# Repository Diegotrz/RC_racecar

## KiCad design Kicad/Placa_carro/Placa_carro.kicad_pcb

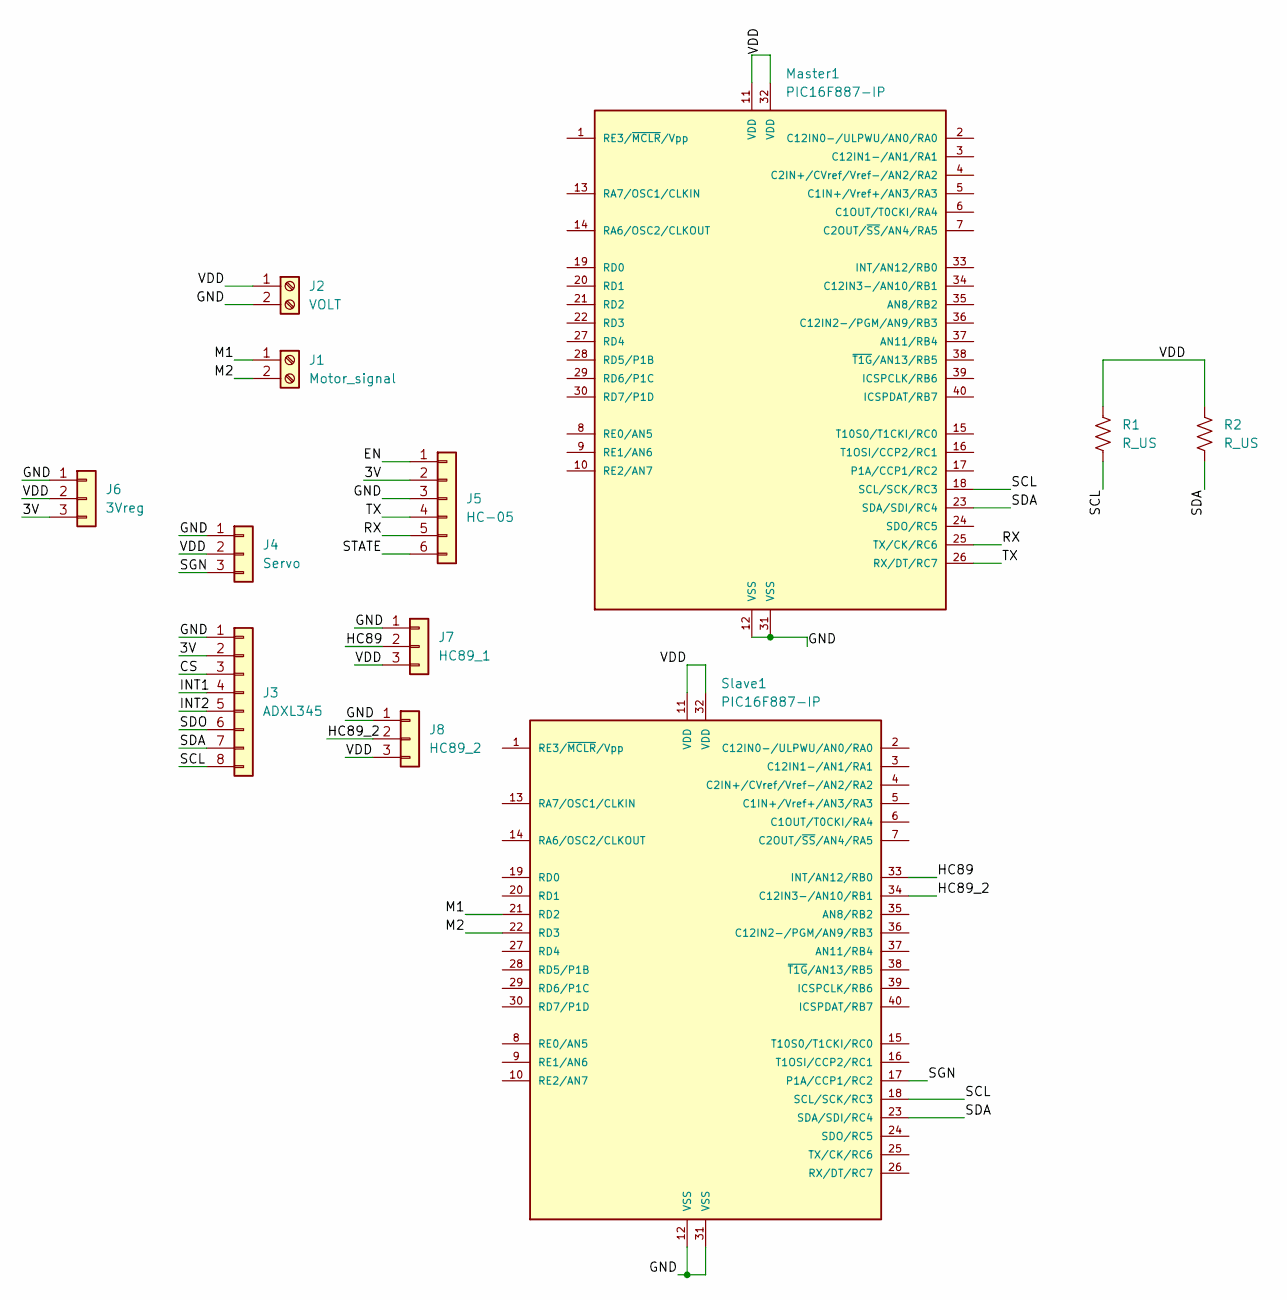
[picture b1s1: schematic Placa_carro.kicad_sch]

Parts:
J1: Motor_signal; TerminalBlock_bornier-2_P5.08mm
J2: VOLT; TerminalBlock_bornier-2_P5.08mm
J3: ADXL345; PinSocket_1x08_P2.54mm_Vertical
J4: Servo; PinHeader_1x03_P2.54mm_Vertical
J5: HC-05; PinSocket_1x06_P2.54mm_Vertical
J6: 3Vreg; PinHeader_1x03_P2.54mm_Vertical
J7: HC89_1; PinHeader_1x03_P2.54mm_Vertical
J8: HC89_2; PinHeader_1x03_P2.54mm_Vertical
Master1: PIC16F887-IP; DIP-40_W15.24mm
R1, R2: R_US; R_Axial_DIN0309_L9.0mm_D3.2mm_P12.70mm_Horizontal
Slave1: PIC16F887-IP; DIP-40_W15.24mm

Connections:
/3V: J3.2, J5.2, J6.3
/CS: J3.3
/EN: J5.1
/GND: J2.2, J3.1, J4.1, J5.3, J6.1, J7.1, J8.1, Master1.12 (VSS), Master1.31 (VSS), Slave1.12 (VSS), Slave1.31 (VSS)
/HC89: J7.2, Slave1.33 (INT/AN12/RB0)
/HC89_2: J8.2, Slave1.34 (C12IN3-/AN10/RB1)
/INT1: J3.4
/INT2: J3.5
/M1: J1.1, Slave1.21 (RD2)
/M2: J1.2, Slave1.22 (RD3)
/RX: J5.5, Master1.25 (TX/CK/RC6)
/SCL: J3.8, Master1.18 (SCL/SCK/RC3), R1.2, Slave1.18 (SCL/SCK/RC3)
/SDA: J3.7, Master1.23 (SDA/SDI/RC4), R2.2, Slave1.23 (SDA/SDI/RC4)
/SDO: J3.6
/SGN: J4.3, Slave1.17 (P1A/CCP1/RC2)
/STATE: J5.6
/TX: J5.4, Master1.26 (RX/DT/RC7)
/VDD: J2.1, J4.2, J6.2, J7.3, J8.3, Master1.11 (VDD), Master1.32 (VDD), R1.1, R2.1, Slave1.11 (VDD), Slave1.32 (VDD)

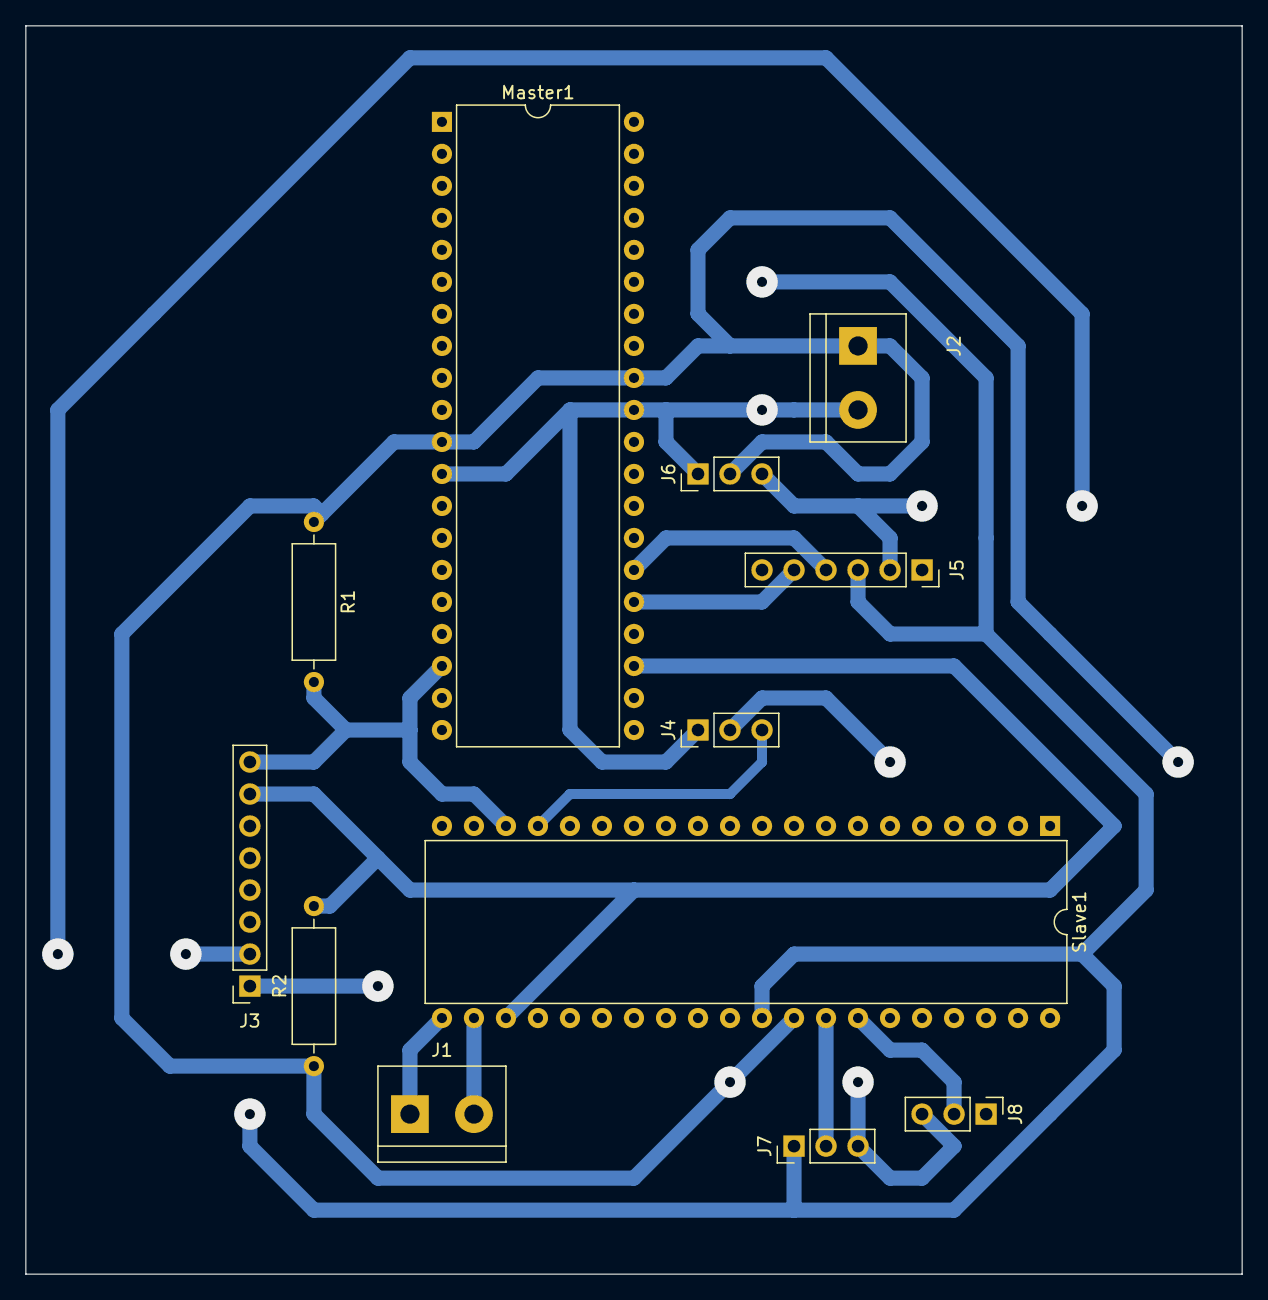
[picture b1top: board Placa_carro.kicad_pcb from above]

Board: 2 copper layers, 96.5 x 99.1 mm, 12 parts (0 on the bottom side), 12 nets.

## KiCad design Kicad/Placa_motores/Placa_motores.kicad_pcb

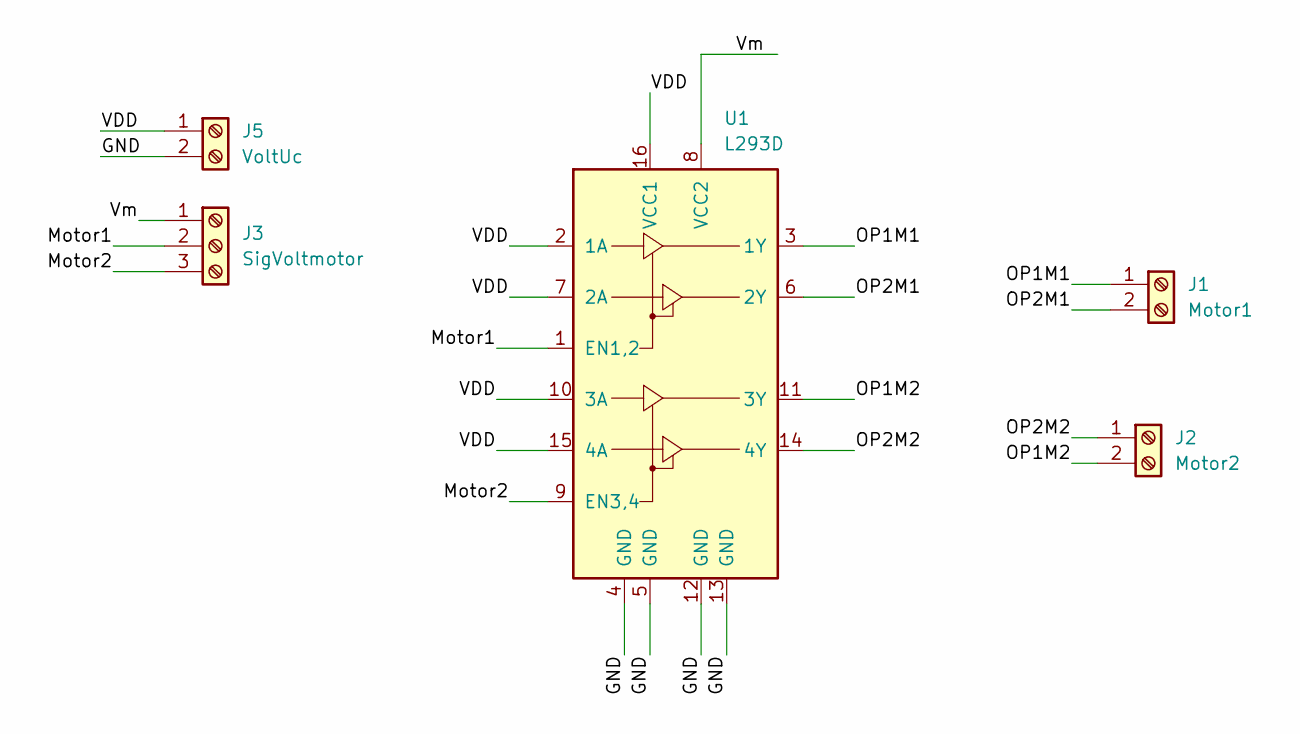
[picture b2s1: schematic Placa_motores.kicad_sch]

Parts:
J1: Motor1; TerminalBlock_bornier-2_P5.08mm
J2: Motor2; TerminalBlock_bornier-2_P5.08mm
J3: SigVoltmotor; TerminalBlock_bornier-3_P5.08mm
J5: VoltUc; TerminalBlock_bornier-2_P5.08mm
U1: L293D; DIP-16_W7.62mm

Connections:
/GND: J5.2, U1.4 (GND), U1.5 (GND), U1.12 (GND), U1.13 (GND)
/Motor1: J3.2, U1.1 (EN1,2)
/Motor2: J3.3, U1.9 (EN3,4)
/OP1M1: J1.1, U1.3 (1Y)
/OP1M2: J2.2, U1.11 (3Y)
/OP2M1: J1.2, U1.6 (2Y)
/OP2M2: J2.1, U1.14 (4Y)
/VDD: J5.1, U1.2 (1A), U1.7 (2A), U1.10 (3A), U1.15 (4A), U1.16 (VCC1)
/Vm: J3.1, U1.8 (VCC2)

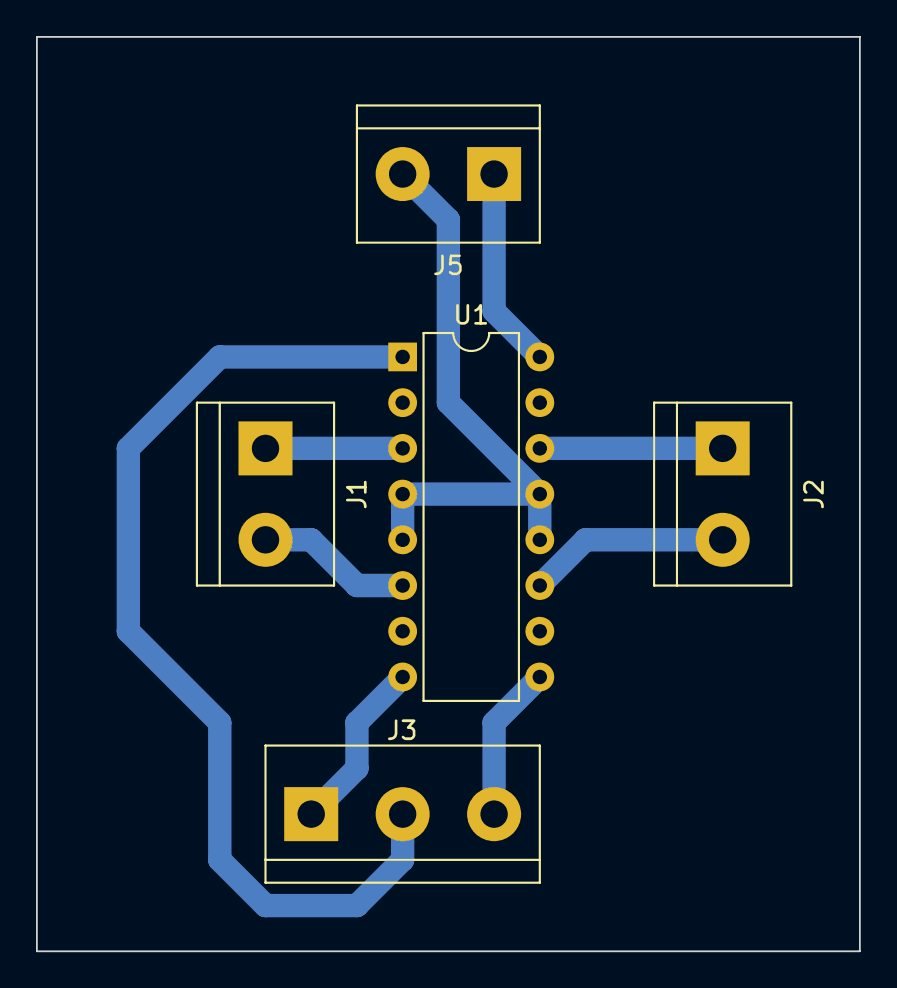
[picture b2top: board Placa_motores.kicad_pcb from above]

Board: 2 copper layers, 45.7 x 50.8 mm, 5 parts (0 on the bottom side), 9 nets.

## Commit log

2023-08-12 Primer pruebas
2023-08-12 Función contador para el HC terminada
2023-08-13 añadido hc
2023-08-13 añadido BT config con UART
2023-08-13 añadido y probado el BT
2023-08-15 Pruebas BT añadidas
2023-08-16 Añadido en Kicad
2023-08-16 Terminada placa motores
2023-08-17 Terminada la placa del carro
2023-08-18 Añadida progra al carro
2023-08-21 Pruebas con adxl345
2023-08-21 Avances varios
    Terminada la placa del carro
    Pruebas avanzadas del esclavo
2023-08-21 Iniciada prueba I2c dos pics
2023-08-22 avances
    a
2023-08-23 Avances
2023-08-24 Pruebas
2023-08-24 mejorado un poco el adxl345
2023-08-25 nuevo
2023-08-25 version final
2023-08-26 Pruebas varias
2023-08-30 Añadidos finales
2023-08-30 placa carro cambiada
